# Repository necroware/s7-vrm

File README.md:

# Necroware's S7-VRM

This project is a Voltage Regulator Module for the Socket 7 mainboards as
defined by Intel in it's Pentium® Processor Flexible Motherboard Design
Guidelines. You can upgrade VRM capable Socket 7 mainboards with this module to
be able to use dual-voltage CPUs like Intel Pentium MMX, AMD K6, AMD K6-2 etc.

*Disclaimer: this VRM can damage your mainboard, CPU or both. Please use at your
own risk.*

__WARNING:__ *inserting the module the wrong way around would put +12V on all
critical lanes. It would destroy the mainboard, the CPU, the memory and all
expansion cards. This can't happen on mainboards with VRM socket, because there
it is not possible to insert it in reverse. On free standing VRM pin header, it
is probably a good idea to cut +12V pin 5 and the unused pin 22 to use them as
a key.*

Youtube Videos:
- Part 1: https://youtu.be/CMiGVQbMC5U
- Part 2: https://youtu.be/J0NLGfocviU
- Part 3: https://youtu.be/kBPp9EAIC8I
- Part 4: https://youtu.be/XV0b5Tvf5gY

## CPU Voltage Type Selection (J1)

There are two kind of socket 7 CPUs, single-voltage and dual-voltage CPUs.
Dual-voltage CPUs are designed to use different voltages for the internal core
and for the I/O. The I/O voltage is specified at 3.3-3.5V, but the core voltage
can be much lower. For the very power efficient AMD K6-III+EE the core voltage
is just 1.6V. 

From revision 0.6 and higher the S7-VRM supports both types of CPUs, where
for the single-voltage CPUs the voltage is completely generated on the module
and for dual-voltage CPUs the I/O voltage is generated by a linear voltage
regulator on the mainboard, where core voltage is generated on the VRM module.

To make this work you have to set the jumper J1 accordingly. Please read which
kind of CPU you have before using this module.

Voltage Type | J1 Pos.  | CPU examples
-------------|----------|---------------------------------------------------
Single       | 1-3, 2-4 | Intel Pentium, AMD K5, Winchip C6, Cyrix M1
Dual         | 1-2, 3-4 | Intel Pentium MMX, AMD K6, Cyrix M1L/MII

## CPU Voltage Selection (SW1)

__WARNING__: Single voltage CPUs are designed to run at 3.3-3.5V everything
below that value could potentially make your system unstable. Everything above
that can damage your mainboard or CPU or both. Dual-voltage CPUs usually need
core voltages far below 3.0V, AMD K6-2 for example expects only 2.2V core
voltage and everything above that can potentially damage the CPU. Always pay
attention to the CPU type you use and apply voltages out of spec only if you
really know what you are doing.

__WARNING__: different revisions can have different voltage settings, please
always pay attention and look into the proper documentation for the revision
you have.

Various voltages can be set using the SW1 switch on the module (0=off, 1=on):

Voltage | Switches | CPU Examples
--------|----------|-------------------------------------------
  1.4V  |  00000   | *Probably too low for any S7 CPU*
  1.5V  |  10000   |
  1.6V  |  01000   | AMD K6-2E+ / K6-3E+ / Mobile K6-2
  1.7V  |  11000   |
  1.8V  |  00100   |
  1.9V  |  10100   |
  2.0V  |  01100   | Cyrix MII (0,18µm version)
  2.1V  |  11100   | 
  2.2V  |  00010   | AMD Mobile K6 / K6-2(+) / K6-3(+)
  2.3V  |  10010   | 
  2.4V  |  01010   | AMD K6-2
  2.5V  |  11010   |
  2.6V  |  00110   | 
  2.7V  |  10110   |
  2.8V  |  01110   | Intel Pentium MMX, IBM 6x86L, Rise MP6 
  2.9V  |  11110   | AMD K6, IBM 6x86MX
  3.0V  |  00011   | 
  3.1V  |  10011   | 
  3.2V  |  01011   | AMD K6@233
  3.3V  |  11011   | Pentium 66-200 (Single Voltage)
  3.4V  |  00111   | 
  3.5V  |  10111   | AMD K5, Winchip C6
  3.6V  |  01111   | 
  3.7V  |  11111   | *Danger: probably to high for any S7 CPU*

## Important remarks

The transistor Q1 with integrated pull-up resistor is optional. It is used for 
enable/disable signal and is unused on most mainbards.

The PCB is made for a through hole inductor, but if you have only SMD it is also
possible to solder that instead. Keep in mind that the inductor has to stand
the required current. Also slightly different inductors are allowed, everything
between 2µH and 4,7µH should work as well. With the higher inductance you get
less current ripple, also voltage ripple can look better, but the maximum
possible current will decrease. Playing with different inductors will also
influence the compensation network.

Capacitors C7 and C8 are used in so called compensation network and are
responsible for DC-DC converter activation and stability. Those parts are very
delicate and dependent on the ESR and values of the output capacitors C9-C12,
and the inductor L1. If your regulator shows stability issues or not starting
at all, try to remove the capacitor C8. If you change any other parts C7, C8 and
R1 have to be adapted accordingly.

When generating Gerber files:

* The title font is "Edo SZ HQ", available online.
* The board dimensions are 53x62mm.

## Bill of materials

Part        | Count | LCSC#    | Comment
------------|-------|----------|--------------------------------------------
C1, C15     | 2     | C13585   | 10u capacitor SMD 1206              
C2, C14     | 2     | C51205   | 4.7u capacitor SMD 1206              
C3, C6, C13 | 3     | C696845  | 0.1u capacitor SMD 1206
C4, C5      | 2     | C407963  | 2200u capacitor TH Radial D10.0mm, P5.00mm
C7          | 1     | C107186  | 220n capacitor SMD 1206
C8          | 1     | C577176  | 39p capacitor SMD 1206
C9-C12      | 4     | C407858  | 1000u capacitor TH Radial D8.0mm, P3.5mm
D1          | 1     | C109000  | Switching diode
J1          | 1     | C2897435 | Connector angled 02x15 pins 2.54mm 
J2          | 1     | N/A      | 2x2 jumper
L1          | 1     | N/A      | 3.3µH inductor
Q1          | 1     | C13871   | NPN-BEC biased transistor 
Q2, Q3      | 2     | C496603  | N-MOSFET GDS at least 15A
Q4          | 1     | C454937  | PNP-BEC biased transistor 
R1, R2, R6  | 3     | C136874  | 15K resistor SMD 1206
R3, R8, R9  | 3     | C706412  | 3,74K resistor SMD 1206
R4          | 1     | C870818  | 5K resistor SMD 1206
R5          | 1     | C137314  | 30K resistor SMD 1206
R7          | 1     | C137115  | 7,5K resistor SMD 1206
SW1         | 1     | C5299506 | DIP-10 Switch THT 5 buttons 2.54mm
U1          | 1     | C382017  | ISL6545 DC-DC Controller

The inductor doesn't need to be very exact, anything between 2.5µH and 4.7µH
should work, but the sweet point is at around 3.3µH. The inductor can be self
made by using a T50 ferrite toroid. For example T50-26 with permeability 75µ
wrapped in 10 loops of 1.3 mm coper.

## Tested mainboards

This module should run with all mainboards, which provide the VRM module header
as specified in Intel Pentium Mainboard Design Guidelines. Most of such boards
were based on Intel Triton (i430FX) and VIA Apolo Master (MV series) chipsets,
but there were also quite a lot of later boards with newer chipsets (f.e.
i430VX), which supported such an external VRM as well.

Most of the mainboards which were equipped with a VRM option, were produced
before Intel Pentium MMX, AMD K6 and other dual-voltage CPUs were officially
available. However those CPUs have changed the multiplier selection behavior of
CPU pins BF0/1. Not only a new pin was introduced for higher multipliers, but
also pin BF0 was not pulled up internally anymore as it has been done on
single-voltage CPUs before. This ended up in wrong multiplier detection on newer
CPUs like Pentium MMX 200, which would be suddenly detected as 166MHz one. This
can be fixed by adding a 10k pull-up resistor to the CPU between pin BF0 I/O
VCC. In the following table of tested mainboards you can find a column R+BF0
which tells if such a pull-up resistor had to be added to properly support the
multiplier settings.

Faster Super Socket 7 CPUs, like AMD K6-2 and newer added another multiplier
selection pin BF2, which is not supported on those old mainboards at all. It
can be added using another mod, but is actually not necessary. If the CPU
multiplier is set to 2x, those newer CPUs would interpret it as 6x and for
66MHz FSB go directly to 400MHz. However to be able to detect the CPU properly
you would need to mod the BIOS. This is however optional, the system should
work also with outdated BIOS. In such a case the CPU just would not be reported
properly. 

With that in mind this VRM was tested using various CPUs and voltages on
following mainboards:

Manufacturer | Model           | Chipset | R+BF0 | BIOS Mod | VRM Compatible
-------------|-----------------|---------|-------|----------|-------------------
Asus         | P/I-P55TP4XE(G) | i430FX  | Yes   | Yes      | Yes
Gigabyte     | GA-586-ATE/P    | i430FX  | Yes   | Yes      | Yes

## License

This work is licensed under the Creative Commons Attribution-ShareAlike 4.0
International License.

## Links
* [Intel Pentium Mainboard Design Guidelines](http://netwinder.osuosl.org/pub/misc/docs/i386/24318702.pdf)

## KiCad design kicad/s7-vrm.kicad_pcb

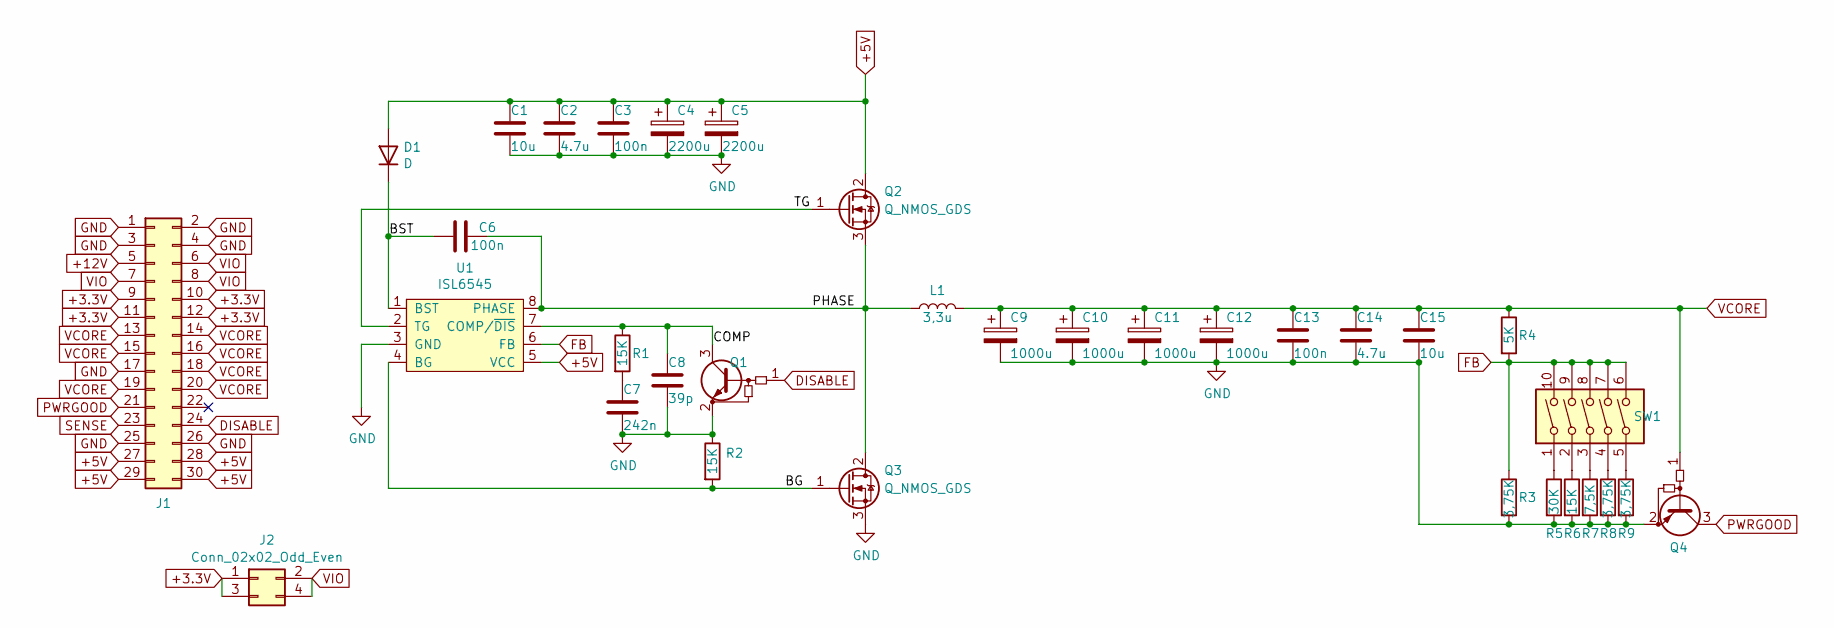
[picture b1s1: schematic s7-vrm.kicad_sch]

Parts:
C1, C15: 10u; C_1206_3216Metric_Pad1.33x1.80mm_HandSolder; LCSC C13585
C2, C14: 4.7u; C_1206_3216Metric_Pad1.33x1.80mm_HandSolder; LCSC C51205
C3, C6, C13: 100n; C_1206_3216Metric_Pad1.33x1.80mm_HandSolder; LCSC C696845
C4, C5: 2200u; CP_Radial_D10.0mm_P5.00mm; LCSC C407963
C7: 242n; C_1206_3216Metric_Pad1.33x1.80mm_HandSolder; LCSC C107186
C8: 39p; C_1206_3216Metric_Pad1.33x1.80mm_HandSolder; LCSC C577176
C9, C10, C11, C12: 1000u; CP_Radial_D8.0mm_P3.50mm; LCSC C407858
D1: D; D_1206_3216Metric_Pad1.42x1.75mm_HandSolder; LCSC C109000
J1: Conn_02x15_Row_Letter_First; PinSocket_2x15_P2.54mm_Horizontal; LCSC C2897435
J2: Conn_02x02_Odd_Even; PinHeader_2x02_P2.54mm_Vertical
L1: 3,3u; L_Toroid_Vertical_L16.0mm_W8.0mm_P7.62mm
Q1: Q_NPN_BEC_BRT; SOT-23; LCSC C13871
Q2, Q3: Q_NMOS_GDS; TO-252-2; LCSC C496603
Q4: Q_PNP_BEC_BRT; SOT-23; LCSC C454937
R1, R2, R6: 15K; R_1206_3216Metric_Pad1.30x1.75mm_HandSolder; LCSC C136874
R3, R8, R9: 3,75K; R_1206_3216Metric_Pad1.30x1.75mm_HandSolder; LCSC C706412
R4: 5K; R_1206_3216Metric_Pad1.30x1.75mm_HandSolder; LCSC C870818
R5: 30K; R_1206_3216Metric_Pad1.30x1.75mm_HandSolder; LCSC C137314
R7: 7,5K; R_1206_3216Metric_Pad1.30x1.75mm_HandSolder; LCSC C137115
SW1: SW_DIP_x05; SW_DIP_SPSTx05_Slide_9.78x14.88mm_W7.62mm_P2.54mm; LCSC C5299506
U1: ISL6545; SOIC-8_3.9x4.9mm_P1.27mm; LCSC C382017

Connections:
+3.3V: J1.9, J1.10, J1.11, J1.12, J2.1, J2.3
+5V: C1.1, C2.1, C3.1, C4.1, C5.1, D1.2 (A), J1.27, J1.28, J1.29, J1.30, Q2.2 (D), U1.5 (VCC)
+12V: J1.5
/BG: Q3.1 (G), R2.2, U1.4 (BG)
/BST: C6.1, D1.1 (K), U1.1 (BST)
/COMP: C8.1, Q1.3 (C), R1.1, U1.7 (COMP/~DIS)
/PHASE: C6.2, L1.1, Q2.3 (S), Q3.2 (D), U1.8 (PHASE)
/TG: Q2.1 (G), U1.2 (TG)
DISABLE: J1.24, Q1.1 (B)
FB: R3.1, R4.2, SW1.6, SW1.7, SW1.8, SW1.9, SW1.10, U1.6 (FB)
GND: C1.2, C2.2, C3.2, C4.2, C5.2, C7.2, C8.2, C9.2, C10.2, C11.2, C12.2, C13.2, C14.2, C15.2, J1.1, J1.2, J1.3, J1.4, J1.17, J1.25, J1.26, Q1.2 (E), Q3.3 (S), Q4.2 (E), R2.1, R3.2, R5.2, R6.2, R7.2, R8.2, R9.2, U1.3 (GND)
unnamed: C7.1, R1.2
unnamed: R5.1, SW1.1
unnamed: R6.1, SW1.2
unnamed: R7.1, SW1.3
unnamed: R8.1, SW1.4
unnamed: R9.1, SW1.5
PWRGOOD: J1.21, Q4.3 (C)
SENSE: J1.23
VCORE: C9.1, C10.1, C11.1, C12.1, C13.1, C14.1, C15.1, J1.13, J1.14, J1.15, J1.16, J1.18, J1.19, J1.20, L1.2, Q4.1 (B), R4.1
VIO: J1.6, J1.7, J1.8, J2.2, J2.4

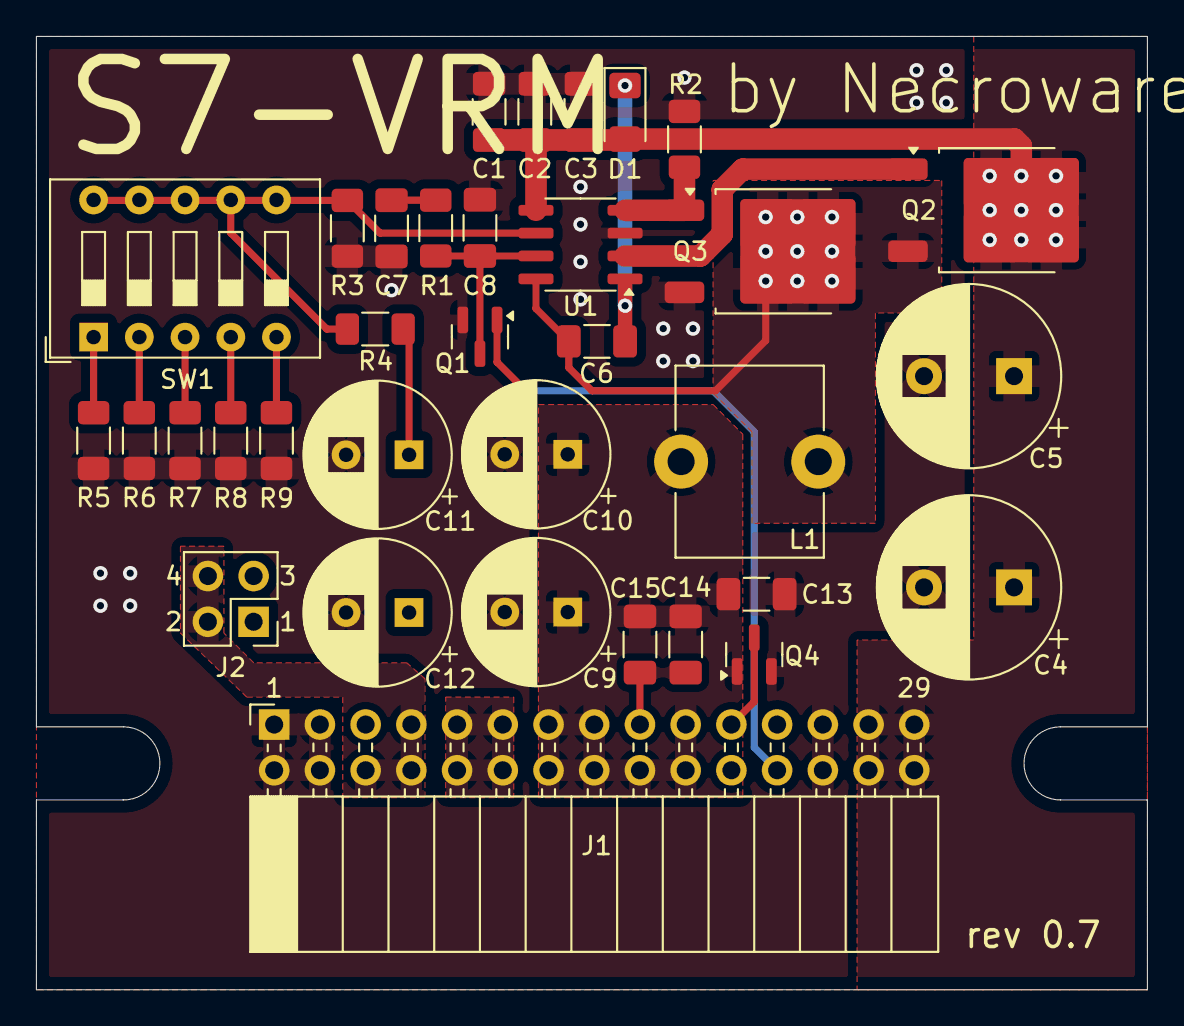
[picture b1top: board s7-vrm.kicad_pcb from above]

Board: 2 copper layers, 61.7 x 53.0 mm, 34 parts (0 on the bottom side), 19 nets.

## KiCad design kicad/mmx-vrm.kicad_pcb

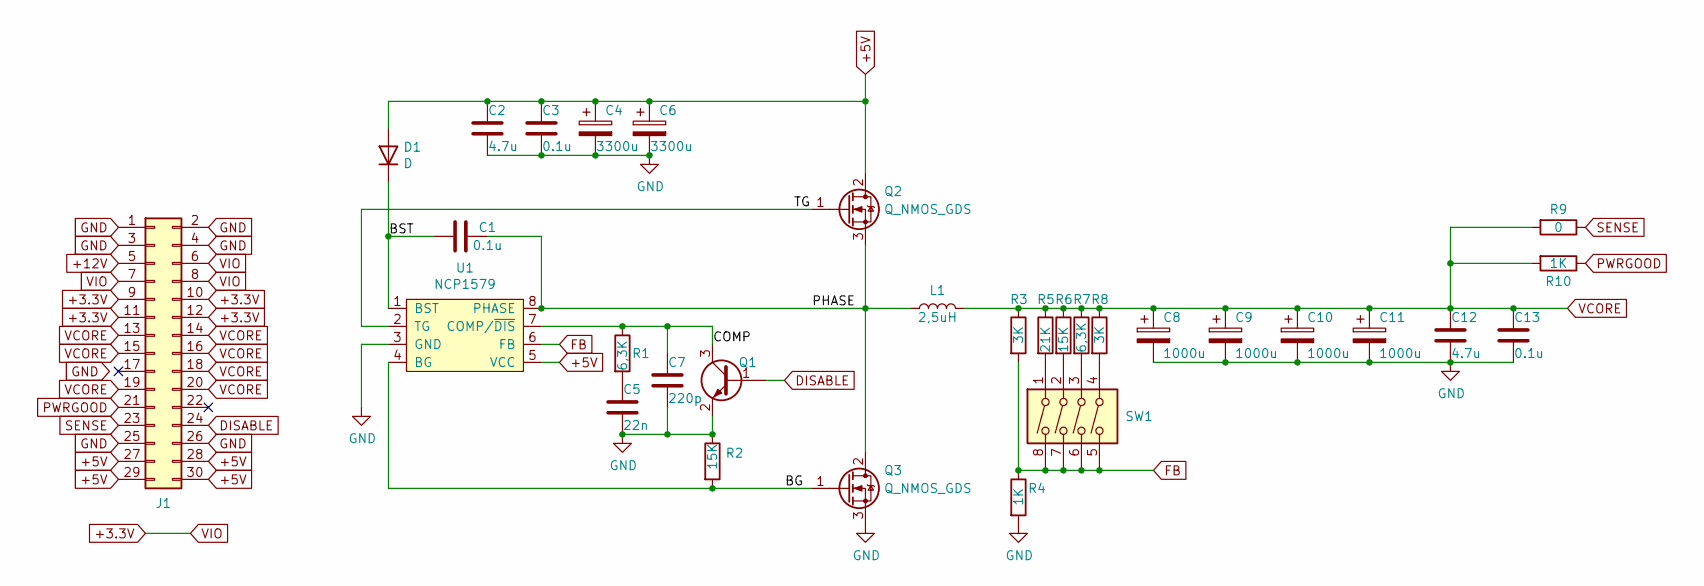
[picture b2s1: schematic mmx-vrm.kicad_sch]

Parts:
C1, C3, C13: 0.1u; C_1206_3216Metric_Pad1.33x1.80mm_HandSolder; LCSC C696845
C2, C12: 4.7u; C_1206_3216Metric_Pad1.33x1.80mm_HandSolder; LCSC C105997
C4, C6: 3300u; CP_Radial_D10.0mm_P5.00mm; LCSC C407862
C5: 22n; C_1206_3216Metric_Pad1.33x1.80mm_HandSolder; LCSC C282848
C7: 220p; C_1206_3216Metric_Pad1.33x1.80mm_HandSolder; LCSC C377077
C8, C9, C10, C11: 1000u; CP_Radial_D8.0mm_P3.50mm; LCSC C407858
D1: D; D_1206_3216Metric_Pad1.42x1.75mm_HandSolder; LCSC C109000
J1: Conn_02x15_Row_Letter_First; PinSocket_2x15_P2.54mm_Horizontal; LCSC C2897435
L1: 2,5uH; L_Toroid_Vertical_L16.0mm_W8.0mm_P7.62mm
Q1: Q_NPN_BEC; SOT-23; LCSC C13871
Q2, Q3: Q_NMOS_GDS; TO-252-2; LCSC C496603
R1, R7: 6,3K; R_1206_3216Metric_Pad1.30x1.75mm_HandSolder; LCSC C229767
R2, R6: 15K; R_1206_3216Metric_Pad1.30x1.75mm_HandSolder; LCSC C144515
R3, R8: 3K; R_1206_3216Metric_Pad1.30x1.75mm_HandSolder; LCSC C229609
R4, R10: 1K; R_1206_3216Metric_Pad1.30x1.75mm_HandSolder; LCSC C144508
R5: 21K; R_1206_3216Metric_Pad1.30x1.75mm_HandSolder; LCSC C229446
R9: 0; R_1206_3216Metric_Pad1.30x1.75mm_HandSolder; LCSC C352163
SW1: SW_DIP_x04; SW_DIP_SPSTx04_Slide_9.78x12.34mm_W7.62mm_P2.54mm; LCSC C15781
U1: NCP1579; SOIC-8_3.9x4.9mm_P1.27mm; LCSC C235991

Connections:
+3.3V: J1.6, J1.7, J1.8, J1.9, J1.10, J1.11, J1.12
+5V: C2.1, C3.1, C4.1, C6.1, D1.2 (A), J1.27, J1.28, J1.29, J1.30, Q2.2 (D), U1.5 (VCC)
+12V: J1.5
/BG: Q3.1 (G), R2.2, U1.4 (BG)
/BST: C1.1, D1.1 (K), U1.1 (BST)
/COMP: C7.1, Q1.3 (C), R1.1, U1.7 (COMP/~DIS)
/PHASE: C1.2, L1.1, Q2.3 (S), Q3.2 (D), U1.8 (PHASE)
/TG: Q2.1 (G), U1.2 (TG)
DISABLE: J1.24, Q1.1 (B)
FB: R3.2, R4.1, SW1.5, SW1.6, SW1.7, SW1.8, U1.6 (FB)
GND: C2.2, C3.2, C4.2, C5.2, C6.2, C7.2, C8.2, C9.2, C10.2, C11.2, C12.2, C13.2, J1.1, J1.2, J1.3, J1.4, J1.25, J1.26, Q1.2 (E), Q3.3 (S), R2.1, R4.2, U1.3 (GND)
unnamed: C5.1, R1.2
unnamed: R5.2, SW1.1
unnamed: R6.2, SW1.2
unnamed: R7.2, SW1.3
unnamed: R8.2, SW1.4
PWRGOOD: J1.21, R10.1
SENSE: J1.23, R9.1
VCORE: C8.1, C9.1, C10.1, C11.1, C12.1, C13.1, J1.13, J1.14, J1.15, J1.16, J1.18, J1.19, J1.20, L1.2, R3.1, R5.1, R6.1, R7.1, R8.1, R9.2, R10.2

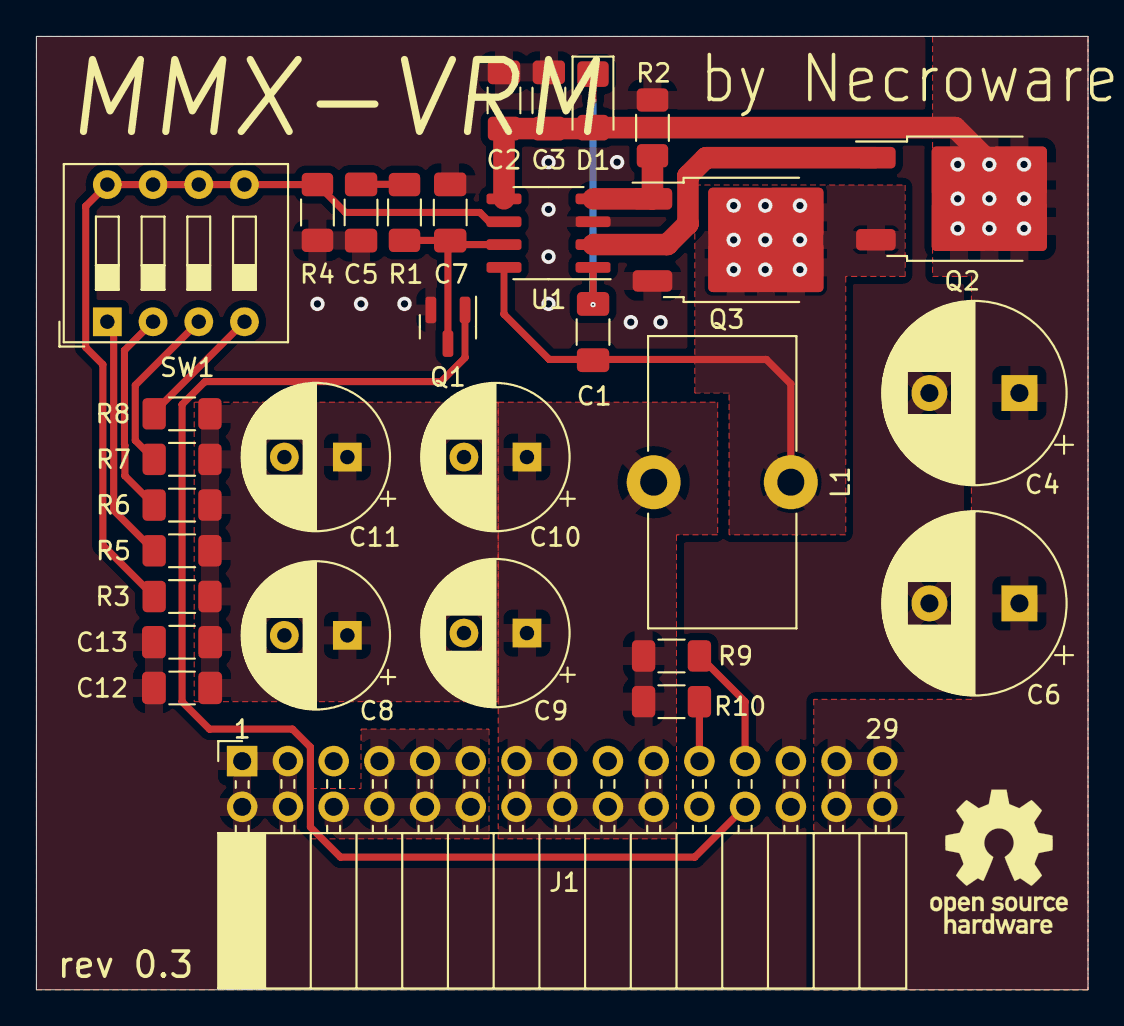
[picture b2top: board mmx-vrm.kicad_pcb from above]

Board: 2 copper layers, 58.4 x 53.0 mm, 31 parts (0 on the bottom side), 18 nets.

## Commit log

2021-08-22 Add gitignore
2021-08-22 Resistors annotation renumber
2021-08-23 Thermal improvements
2021-08-23 Minor layout improvements
2021-09-06 Improve clearance, rev 0.3 started
2021-10-23 LCSC number for the voltage regulator
2021-11-19 Fixes after first tests
2021-11-19 Readjusted the resistors for 3.2V support
2021-11-19 Renamed project into s7-vrm
2021-11-19 Readme added
2021-11-20 Tweaked lower voltages
2021-11-20 Added docs
2021-11-20 Revert "Renamed project into s7-vrm"
    This reverts commit abb7c84a7e06dd52f3d76b1c246c1366ac80b644.
2021-12-02 First raw version
2021-12-02 Improved power lines
2021-12-14 Add LCSC IDs and documentation
2022-01-04 Minor fixes.
    - Changed LCSC part numbers (due to shortage)
    - Enlarged GND plane distance
2023-02-26 Switched to KiCad 7
2023-03-27 Wide version
2023-03-30 Updated parameters
2023-04-01 Renamed project
2023-04-01 Revision 0.4
    - Added optional 1uF capacitors on input and output
    - Increased the size of the inductor pins for SMD option
    - Minor layout fixes
    - Updated silk layer, logos etc.
2023-04-01 Updated documentation and part numbers
2023-04-01 Updated logos, readme and photo
2023-04-03 Calculations fixes
2023-04-03 Layout improvements
2023-04-03 Fixed BOM in readme, fixed part numbers in schematics
2023-04-03 Update parts numbers
2023-04-09 Layout improvements, added slits for the clips
2023-04-12 Fixed resistor labels in the calculations
2023-04-12 Add license file
2023-04-12 Deleted intel documents to avoid any legal issues
2023-04-12 Updated picture
2023-04-12 Added YT links
2023-04-22 Updated parts and documenttion
2023-04-22 Set suggested coild wire to 1.3mm
2023-04-22 Prepared rev 0.5
    - Increased voltage range now 1.6-3.5V
    - Moved FB resistors to lower part
    - Reduced the height slightly
    - Improved location of filter caps
    - Unified some resistors values
2023-04-22 Updated parts, fixed project after broken merge
2023-04-23 Increase PCB width slightly
2023-04-28 Take shorter input capacitor
2023-04-28 Updated image
2023-04-29 Added video part 4 link
2023-04-30 Update R calculations
2023-05-01 Added module orientation warning.
2023-05-08 Using sence to FB and transistor for PWRGOOD
2023-07-12 Work in progress
2023-07-13 Added alternative resistor values for ISL6545
2023-07-13 Added ISL6545 part number
2023-12-29 Prepared for production
2024-01-09 Update LCSC parts and values
2024-06-06 Swap R3 and R4 to get proper voltage
2024-06-23 prepare rev 0.6
2024-06-23 updated readme and bom
2024-06-23 Update picture
2024-06-23 fix readme
2024-06-23 update list of tested mainboards
2024-06-25 minor layout fixes
2024-06-25 silk layer fixes
2024-06-25 changed edge infill
2024-06-25 add gerber subfolder to export settings
2024-08-22 readme fixes
2024-08-31 Update component values based on LCSC numbers, add Gerber notes.
2025-01-03 Drop sense pin usage.
    Some mainboards don't implement sense pin properly and have other
    signals connected to that pin. This can lead to invalid output voltage
    reading. In the worst case sense could be bound to ground, which would
    report 0V to the controller all the time, which would try to ramp up
    the voltage to the maximum of about 4.4V. This could potentially kill
    the CPU, especially low voltage K6-II or similar.
